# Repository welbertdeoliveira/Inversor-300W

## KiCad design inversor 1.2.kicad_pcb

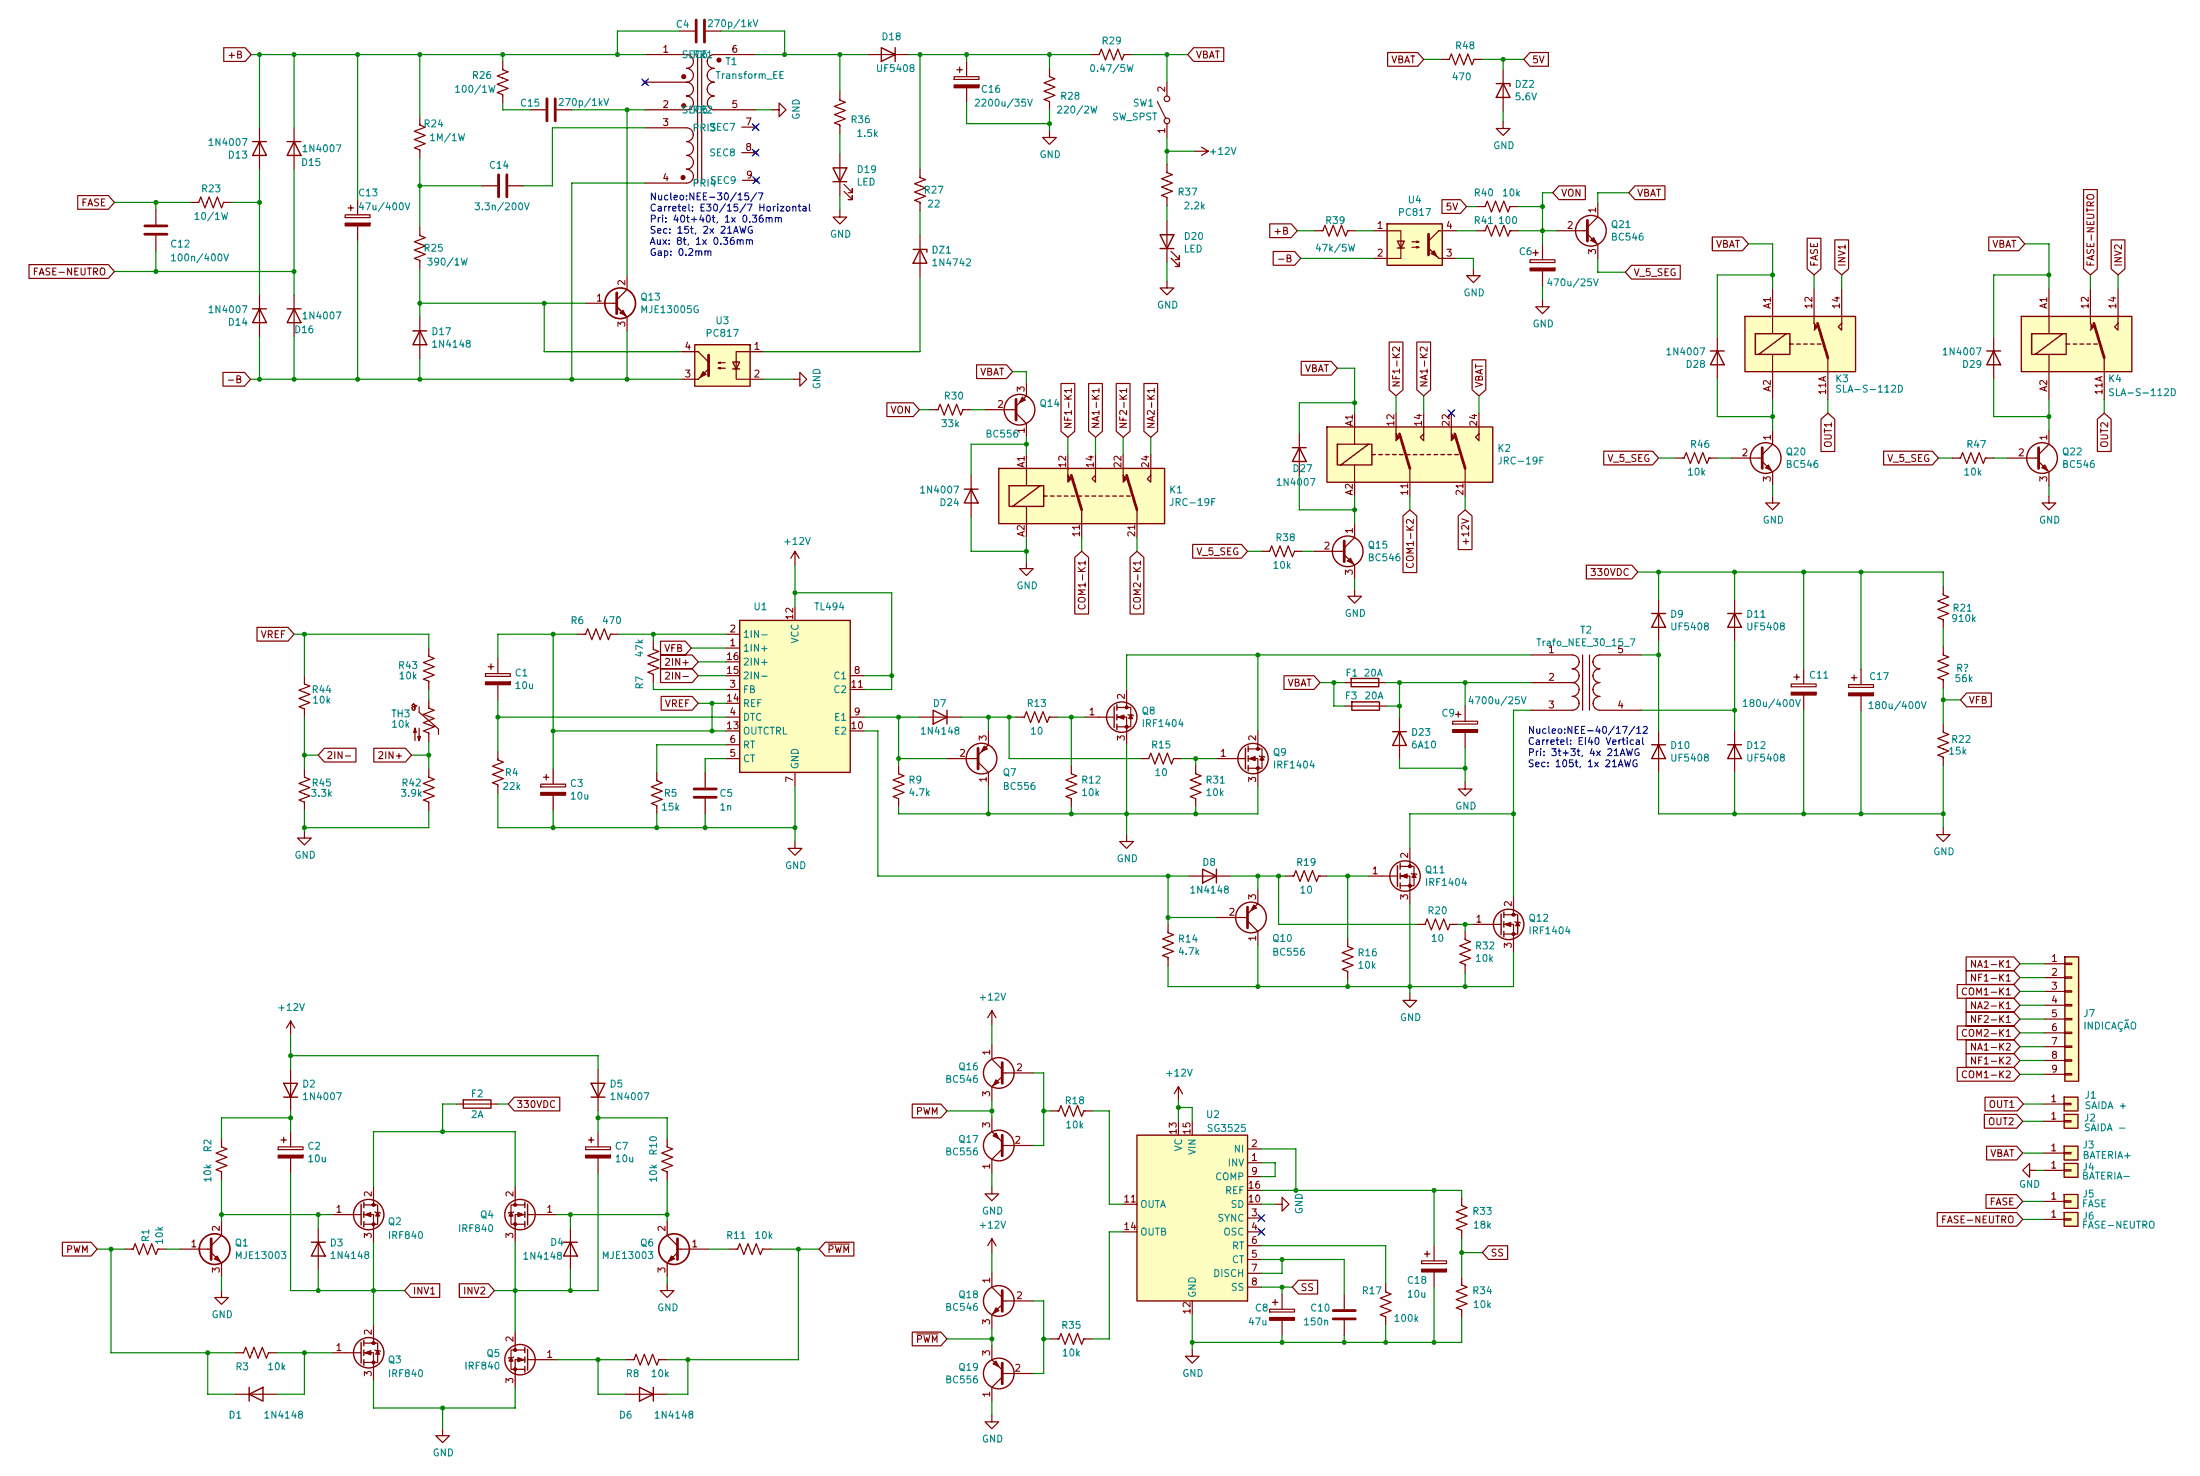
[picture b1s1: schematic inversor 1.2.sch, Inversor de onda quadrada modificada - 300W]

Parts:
C1, C2, C3, C7, C18: 10u; CP_Radial_D6.3mm_P2.50mm
C4, C15: 270p/1kV; C_Axial_L3.8mm_D2.6mm_P10.00mm_Horizontal
C5: 1n; C_Axial_L3.8mm_D2.6mm_P10.00mm_Horizontal
C6: 470u/25V; CP_Radial_D18.0mm_P7.50mm
C8: 47u; CP_Radial_D6.3mm_P2.50mm
C9: 4700u/25V; CP_Radial_D18.0mm_P7.50mm
C10: 150n; C_Axial_L3.8mm_D2.6mm_P10.00mm_Horizontal
C11, C17: 180u/400V; CP_Radial_D16.0mm_P7.50mm
C12: 100n/400V; C_Axial_L3.8mm_D2.6mm_P15.00mm_Horizontal
C13: 47u/400V; CP_Radial_D16.0mm_P7.50mm
C14: 3.3n/200V; C_Axial_L3.8mm_D2.6mm_P10.00mm_Horizontal
C16: 2200u/35V; CP_Radial_D18.0mm_P7.50mm
D1, D3, D4, D6, D7, D8, D17: 1N4148; D_DO-35_SOD27_P7.62mm_Horizontal
D2, D5, D13, D14, D15, D16, D24, D27, D28, D29: 1N4007; D_DO-41_SOD81_P10.16mm_Horizontal
D9, D10, D11, D12, D18: UF5408; D_DO-201AD_P15.24mm_Horizontal
D19, D20: LED; LED_D3.0mm
D23: 6A10; D_DO-201AD_P15.24mm_Horizontal
DZ1: 1N4742; D_DO-35_SOD27_P7.62mm_Horizontal
DZ2: 5.6V; D_DO-35_SOD27_P7.62mm_Horizontal
F1, F3: 20A; Fusivel_lamina_medio
F2: 2A; Fuseholder_Cylinder-5x20mm_Stelvio-Kontek_PTF78_Horizontal_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
J1: SAIDA +; TerminalBlock_bornier-2_P5.08mm
J2: SAIDA -; TerminalBlock_bornier-2_P5.08mm
J3: BATERIA+; TerminalBlock_bornier-2_P5.08mm
J4: BATERIA-; TerminalBlock_bornier-2_P5.08mm
J5: FASE; TerminalBlock_bornier-2_P5.08mm
J6: FASE-NEUTRO; TerminalBlock_bornier-2_P5.08mm
J7: INDICAÇÃO; TerminalBlock_RND_205-00008_1x09_P5.00mm_Horizontal
K1, K2: JRC-19F; Relay_DPDT_Finder_30.22
K3, K4: SLA-S-112D; Relay_SPDT_RAYEX-L90
Q1, Q6: MJE13003; TO-126-3_Vertical
Q2, Q3, Q4, Q5: IRF840; TO-220-3_Vertical
Q7, Q10, Q14, Q17, Q19: BC556; TO-92_Wide
Q8, Q9, Q11, Q12: IRF1404; TO-220-3_Vertical
Q13: MJE13005G; TO-220-3_Vertical
Q15, Q16, Q18, Q20, Q21, Q22: BC546; TO-92_Wide
R1, R2, R3, R8, R10, R11, R12, R16, R18, R31, R32, R34, R35, R38, R40, R43, R44, R46, R47: 10k; R_Axial_DIN0207_L6.3mm_D2.5mm_P10.16mm_Horizontal
R4: 22k; R_Axial_DIN0207_L6.3mm_D2.5mm_P10.16mm_Horizontal
R5, R22: 15k; R_Axial_DIN0207_L6.3mm_D2.5mm_P10.16mm_Horizontal
R6, R48: 470; R_Axial_DIN0207_L6.3mm_D2.5mm_P10.16mm_Horizontal
R7: 47k; R_Axial_DIN0207_L6.3mm_D2.5mm_P10.16mm_Horizontal
R9, R14: 4.7k; R_Axial_DIN0207_L6.3mm_D2.5mm_P10.16mm_Horizontal
R13, R15, R19, R20: 10; R_Axial_DIN0207_L6.3mm_D2.5mm_P10.16mm_Horizontal
R17: 100k; R_Axial_DIN0207_L6.3mm_D2.5mm_P10.16mm_Horizontal
R21: 910k; R_Axial_DIN0207_L6.3mm_D2.5mm_P10.16mm_Horizontal
R23: 10/1W; R_Axial_DIN0207_L6.3mm_D2.5mm_P10.16mm_Horizontal
R24: 1M/1W; R_Axial_DIN0207_L6.3mm_D2.5mm_P10.16mm_Horizontal
R25: 390/1W; R_Axial_DIN0207_L6.3mm_D2.5mm_P10.16mm_Horizontal
R26: 100/1W; R_Axial_DIN0207_L6.3mm_D2.5mm_P10.16mm_Horizontal
R27: 22; R_Axial_DIN0207_L6.3mm_D2.5mm_P10.16mm_Horizontal
R28: 220/2W; R_Axial_DIN0207_L6.3mm_D2.5mm_P10.16mm_Horizontal
R29: 0.47/5W; R_Axial_DIN0309_L9.0mm_D3.2mm_P20.32mm_Horizontal
R30: 33k; R_Axial_DIN0207_L6.3mm_D2.5mm_P10.16mm_Horizontal
R33: 18k; R_Axial_DIN0207_L6.3mm_D2.5mm_P10.16mm_Horizontal
R36: 1.5k; R_Axial_DIN0207_L6.3mm_D2.5mm_P10.16mm_Horizontal
R37: 2.2k; R_Axial_DIN0207_L6.3mm_D2.5mm_P10.16mm_Horizontal
R39: 47k/5W; R_Axial_DIN0207_L6.3mm_D2.5mm_P10.16mm_Horizontal
R41: 100; R_Axial_DIN0207_L6.3mm_D2.5mm_P10.16mm_Horizontal
R42: 3.9k; R_Axial_DIN0207_L6.3mm_D2.5mm_P10.16mm_Horizontal
R45: 3.3k; R_Axial_DIN0207_L6.3mm_D2.5mm_P10.16mm_Horizontal
SW1: SW_SPST; TerminalBlock_bornier-2_P5.08mm
T1: Transform_EE; Trafo_NEE_30_7_7
T2: Trafo_NEE_30_15_7
TH3: 10k; TerminalBlock_bornier-2_P5.08mm
U1: TL494; DIP-16_W7.62mm_Socket_LongPads
U2: SG3525; DIP-16_W7.62mm_Socket_LongPads
U3, U4: PC817; DIP-4_W7.62mm

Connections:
2IN+: R42.2, TH3.2, U1.16 (2IN+)
2IN-: R44.1, R45.2, U1.15 (2IN-)
5V: DZ2.1 (K), R40.1, R48.2
330VDC: C11.1, C17.1, D9.1 (K), D11.1 (K), F2.1, R21.2
+12V: D2.2 (A), D5.2 (A), K2.21, Q16.1 (C), Q18.1 (C), R37.2, SW1.1 (A), U1.8 (C1), U1.11 (C2), U1.12 (VCC), U2.13 (VC), U2.15 (VIN)
+B: C4.1, C13.1, D13.1 (K), D15.1 (K), R24.2, R26.2, R39.1, T1.1 (PR1)
-B: C13.2, D14.2 (A), D16.2 (A), D17.2 (A), Q13.3 (E), T1.4 (PRI4), U3.3, U4.2
COM1-RL1: J7.3, K1.11
COM1-RL2: J7.9, K2.11
COM2-RL1: J7.6, K1.21
FASE: C12.1, J5.1, K3.12, R23.2
FASE-NEUTRO: C12.2, D15.2 (A), D16.1 (K), J6.1, K4.12
GND: C3.2, C5.2, C6.2, C8.2, C9.2, C10.2, C11.2, C16.2, C17.2, C18.2, D10.2 (A), D12.2 (A), D19.1 (K), D20.1 (K), D23.2 (A), D24.2 (A), DZ2.2 (A), J4.1, J4.2, K1.A2, Q1.3 (E), Q3.3 (S), Q5.3 (S), Q6.3 (E), Q7.1 (C), Q8.3 (S), Q9.3 (S), Q10.1 (C), Q11.3 (S), Q12.3 (S), Q15.3 (E), Q17.1 (C), Q19.1 (C), Q20.3 (E), Q22.3 (E), R4.1, R5.1, R9.2, R12.2, R14.2, R16.2, R17.1, R22.1, R28.1, R31.2, R32.2, R34.1, R42.1, R45.1, T1.5 (SEC5), U1.7 (GND), U2.10 (SD), U2.12 (GND), U3.2, U4.3
INV1: C2.2, D3.2 (A), K3.14, Q2.3 (S), Q3.2 (D)
INV2: C7.2, D4.2 (A), K4.14, Q4.3 (S), Q5.2 (D)
NA1-RL1: J7.1, K1.14
NA1-RL2: J7.7, K2.14
NA2-RL1: J7.4, K1.24
NF1-RL1: J7.2, K1.12
NF1-RL2: J7.8, K2.12
NF2-RL1: J7.5, K1.22
unnamed: C1.2, R4.2, U1.4 (DTC)
unnamed: C2.1, D2.1 (K), R2.1
unnamed: C4.2, D18.2 (A), R36.2, T1.6 (SEC6)
unnamed: C5.1, U1.5 (CT)
unnamed: C7.1, D5.1 (K), R10.1
unnamed: C9.1, D23.1 (K), F1.1, F3.1, T2.2 (PM)
unnamed: C10.1, U2.5 (CT), U2.7 (DISCH)
unnamed: C14.1, R24.1, R25.2
unnamed: C14.2, T1.3 (PRI3)
unnamed: C15.1, R26.1
unnamed: C15.2, Q13.2 (C), T1.2 (PR2)
unnamed: C16.1, D18.1 (K), R27.2, R28.2, R29.1
unnamed: C18.1, R33.2, U2.2 (NI), U2.16 (REF)
unnamed: D1.2 (A), Q3.1 (G), R3.2
unnamed: D3.1 (K), Q1.2 (C), Q2.1 (G), R2.2
unnamed: D4.1 (K), Q4.1 (G), Q6.2 (C), R10.2
unnamed: D6.2 (A), Q5.1 (G), R8.2
unnamed: D7.1 (K), Q7.3 (E), R13.2, R15.2
unnamed: D7.2 (A), Q7.2 (B), R9.1, U1.9 (E1)
unnamed: D8.1 (K), Q10.3 (E), R19.2, R20.2
unnamed: D8.2 (A), Q10.2 (B), R14.1, U1.10 (E2)
unnamed: D9.2 (A), D10.1 (K), T2.5 (S2)
unnamed: D11.2 (A), D12.1 (K), T2.4 (S1)
unnamed: D13.2 (A), D14.1 (K), R23.1
unnamed: D17.1 (K), Q13.1 (B), R25.1, U3.4
unnamed: D19.2 (A), R36.1
unnamed: D20.2 (A), R37.1
unnamed: D24.1 (K), K1.A1, Q14.1 (C)
unnamed: D27.2 (A), K2.A2, Q15.1 (C)
unnamed: D28.2 (A), K3.A2, Q20.1 (C)
unnamed: D29.2 (A), K4.A2, Q22.1 (C)
unnamed: DZ1.1 (K), R27.1
unnamed: DZ1.2 (A), U3.1
unnamed: F2.2, Q2.2 (D), Q4.2 (D)
unnamed: Q1.1 (B), R1.1
unnamed: Q6.1 (B), R11.2
unnamed: Q8.1 (G), R12.1, R13.1
unnamed: Q8.2 (D), Q9.2 (D), T2.1 (PR1)
unnamed: Q9.1 (G), R15.1, R31.1
unnamed: Q11.1 (G), R16.1, R19.1
unnamed: Q11.2 (D), Q12.2 (D), T2.3 (PR2)
unnamed: Q12.1 (G), R20.1, R32.1
unnamed: Q14.2 (B), R30.2
unnamed: Q15.2 (B), R38.2
unnamed: Q16.2 (B), Q17.2 (B), R18.1
unnamed: Q18.2 (B), Q19.2 (B), R35.1
unnamed: Q20.2 (B), R46.2
unnamed: Q22.2 (B), R47.2
unnamed: R5.2, U1.6 (RT)
unnamed: R6.2, R7.2, U1.2 (1IN-)
unnamed: R7.1, U1.3 (FB)
unnamed: R17.2, U2.6 (RT)
unnamed: R18.2, U2.11 (OUTA)
unnamed: R35.2, U2.14 (OUTB)
unnamed: R39.2, U4.1
unnamed: R41.1, U4.4
unnamed: R43.1, TH3.1
unnamed: U2.1 (INV), U2.9 (COMP)
OUT1: J1.1, J1.2, K3.11A, K3.11B
OUT2: J2.1, J2.2, K4.11A, K4.11B
PWM: D1.1 (K), Q16.3 (E), Q17.3 (E), R1.2, R3.1
SS: C8.1, R33.1, R34.2, U2.8 (SS)
VBAT: D27.1 (K), D28.1 (K), D29.1 (K), F1.2, F3.2, J3.1, J3.2, K2.24, K2.A1, K3.A1, K4.A1, Q14.3 (E), Q21.1 (C), R29.2, R48.1, SW1.2 (B)
VFB: R21.1, R22.2, U1.1 (1IN+)
VON: C6.1, Q21.2 (B), R30.1, R40.2, R41.2
VREF: C1.1, C3.1, R6.1, R43.2, R44.2, U1.13 (OUTCTRL), U1.14 (REF)
V_5_SEG: Q21.3 (E), R38.1, R46.1, R47.1
~PWM: D6.1 (K), Q18.3 (E), Q19.3 (E), R8.1, R11.1

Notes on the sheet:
Nucleo:NEE-40/17/12 Carretel: EI40 Vertical Pri: 3t+3t, 4x 21AWG Sec: 105t, 1x 21AWG
Nucleo:NEE-30/15/7 Carretel: E30/15/7 Horizontal Pri: 40t+40t, 1x 0.36mm Sec: 15t, 2x 21AWG Aux: 8t, 1x 0.36mm Gap: 0.2mm

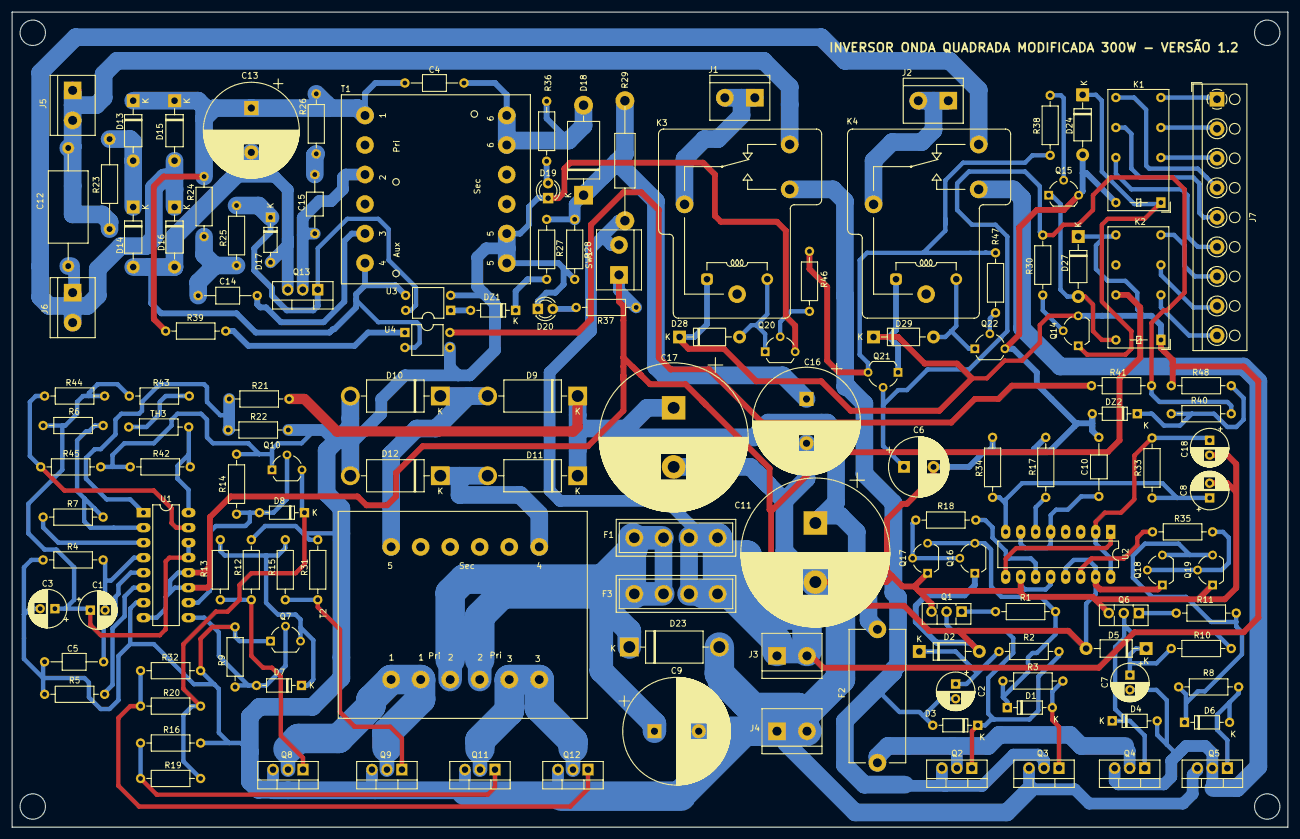
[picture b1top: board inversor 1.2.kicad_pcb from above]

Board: 2 copper layers, 216.0 x 138.0 mm, 137 parts (0 on the bottom side), 89 nets.

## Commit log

2022-03-06 Inversor 300W
    Inversor 300W, de onda quadrada modificada, com rendiemento de 80% em plena carga. Contém carregador de bateria e proteção térmica. Operacional e funcionando. Arquivos em KiCAD.
